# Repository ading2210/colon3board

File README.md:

# colon3board

This is a custom designed mechanical keyboard, created for the the [Hackpad](https://hackpad.hackclub.com/) event. It has a full sized 104 key layout, and a built in OLED display.

I designed this so I could get more practice with designing PCBs in KiCad and with modeling larger parts in Fusion 360. Also, I get to have a free keyboard in the end thanks to the grant from Hack Club. 

## BOM

### For PCB:
| Part                                  | Count (needed) | Count (purchased) | Price  | Shipping Cost | Link                                                                                          |
|---------------------------------------|----------------|-------------------|--------|---------------|-----------------------------------------------------------------------------------------------|
| Raspberry Pi Pico                     | 1              | 0                 | $0.00  | $0.00         | https://www.amazon.com/Raspberry-RP2040-microcontroller-Dual-core-Processor-1pc/dp/B0BK9CTMSV |
| SSD1306 128x32 OLED                   | 1              | 1                 | $2.32  | $0.00         | https://www.aliexpress.us/item/3256805123611667.html                                          |
| Cherry MX key switches                | 104            | 108               | $32.99 | $0.00         | https://www.amazon.com/Zjmehty-Switches-Mechanical-Pre-Lubed-Pin-Enhanced/dp/B0CF8DWDGF       |
| PBT Keycaps                           | 104            | 139               | $13.99 | $0.00         | https://www.amazon.com/Doubleshot-Mechanical-Keyboard-Compatiability-Keyboads/dp/B0F7H32LKC   |
| PCB Mount Stabilizers Kit             | 1              | 1                 | $9.99  | $0.00         | https://www.amazon.com/GLORIOUS-Stabilizer-Mechanical-Keyboards-Compatible/dp/B09MZKFLXP      |
| 1x4 2.54mm vertical female pin header | 1              | 1                 | $0.25  | $4.99         | https://www.digikey.com/en/products/detail/adam-tech/RS1-04-G/9829303                         |
| 1x4 2.54mm vertical male pin header   | 1              | 1                 | $0.20  | $0.00         | https://www.digikey.com/en/products/detail/metz-connect-usa-inc/PR20204VBNN/12342903          |
| MCP23008 IO expander                  | 1              | 1                 | $1.54  | $0.00         | https://www.digikey.com/en/products/detail/microchip-technology/MCP23008-E-P/735951           |
| 1N4148 diodes                         | 104            | 110               | $3.72  | $0.00         | https://www.digikey.com/en/products/detail/onsemi/1N4148-T50A/978509                          |
| PCB Fabrication from JLCPCB           | 1              | 5                 | $25.80 | $52.08        | https://jlcpcb.com/                                                                           |

### For Case:
- Case is 3d printed in PLA
- 6x M2x5 screw
- 4x M3x12 screw
- 4x M3x4 heat set inserts

## License

This project is licensed under the GNU GPL v3.

```
ading2210/colon3board - A custom mechanical keyboard
Copyright (C) 2025 ading2210

This program is free software: you can redistribute it and/or modify
it under the terms of the GNU General Public License as published by
the Free Software Foundation, either version 3 of the License, or
(at your option) any later version.

This program is distributed in the hope that it will be useful,
but WITHOUT ANY WARRANTY; without even the implied warranty of
MERCHANTABILITY or FITNESS FOR A PARTICULAR PURPOSE.  See the
GNU General Public License for more details.

You should have received a copy of the GNU General Public License
along with this program.  If not, see <https://www.gnu.org/licenses/>.
```

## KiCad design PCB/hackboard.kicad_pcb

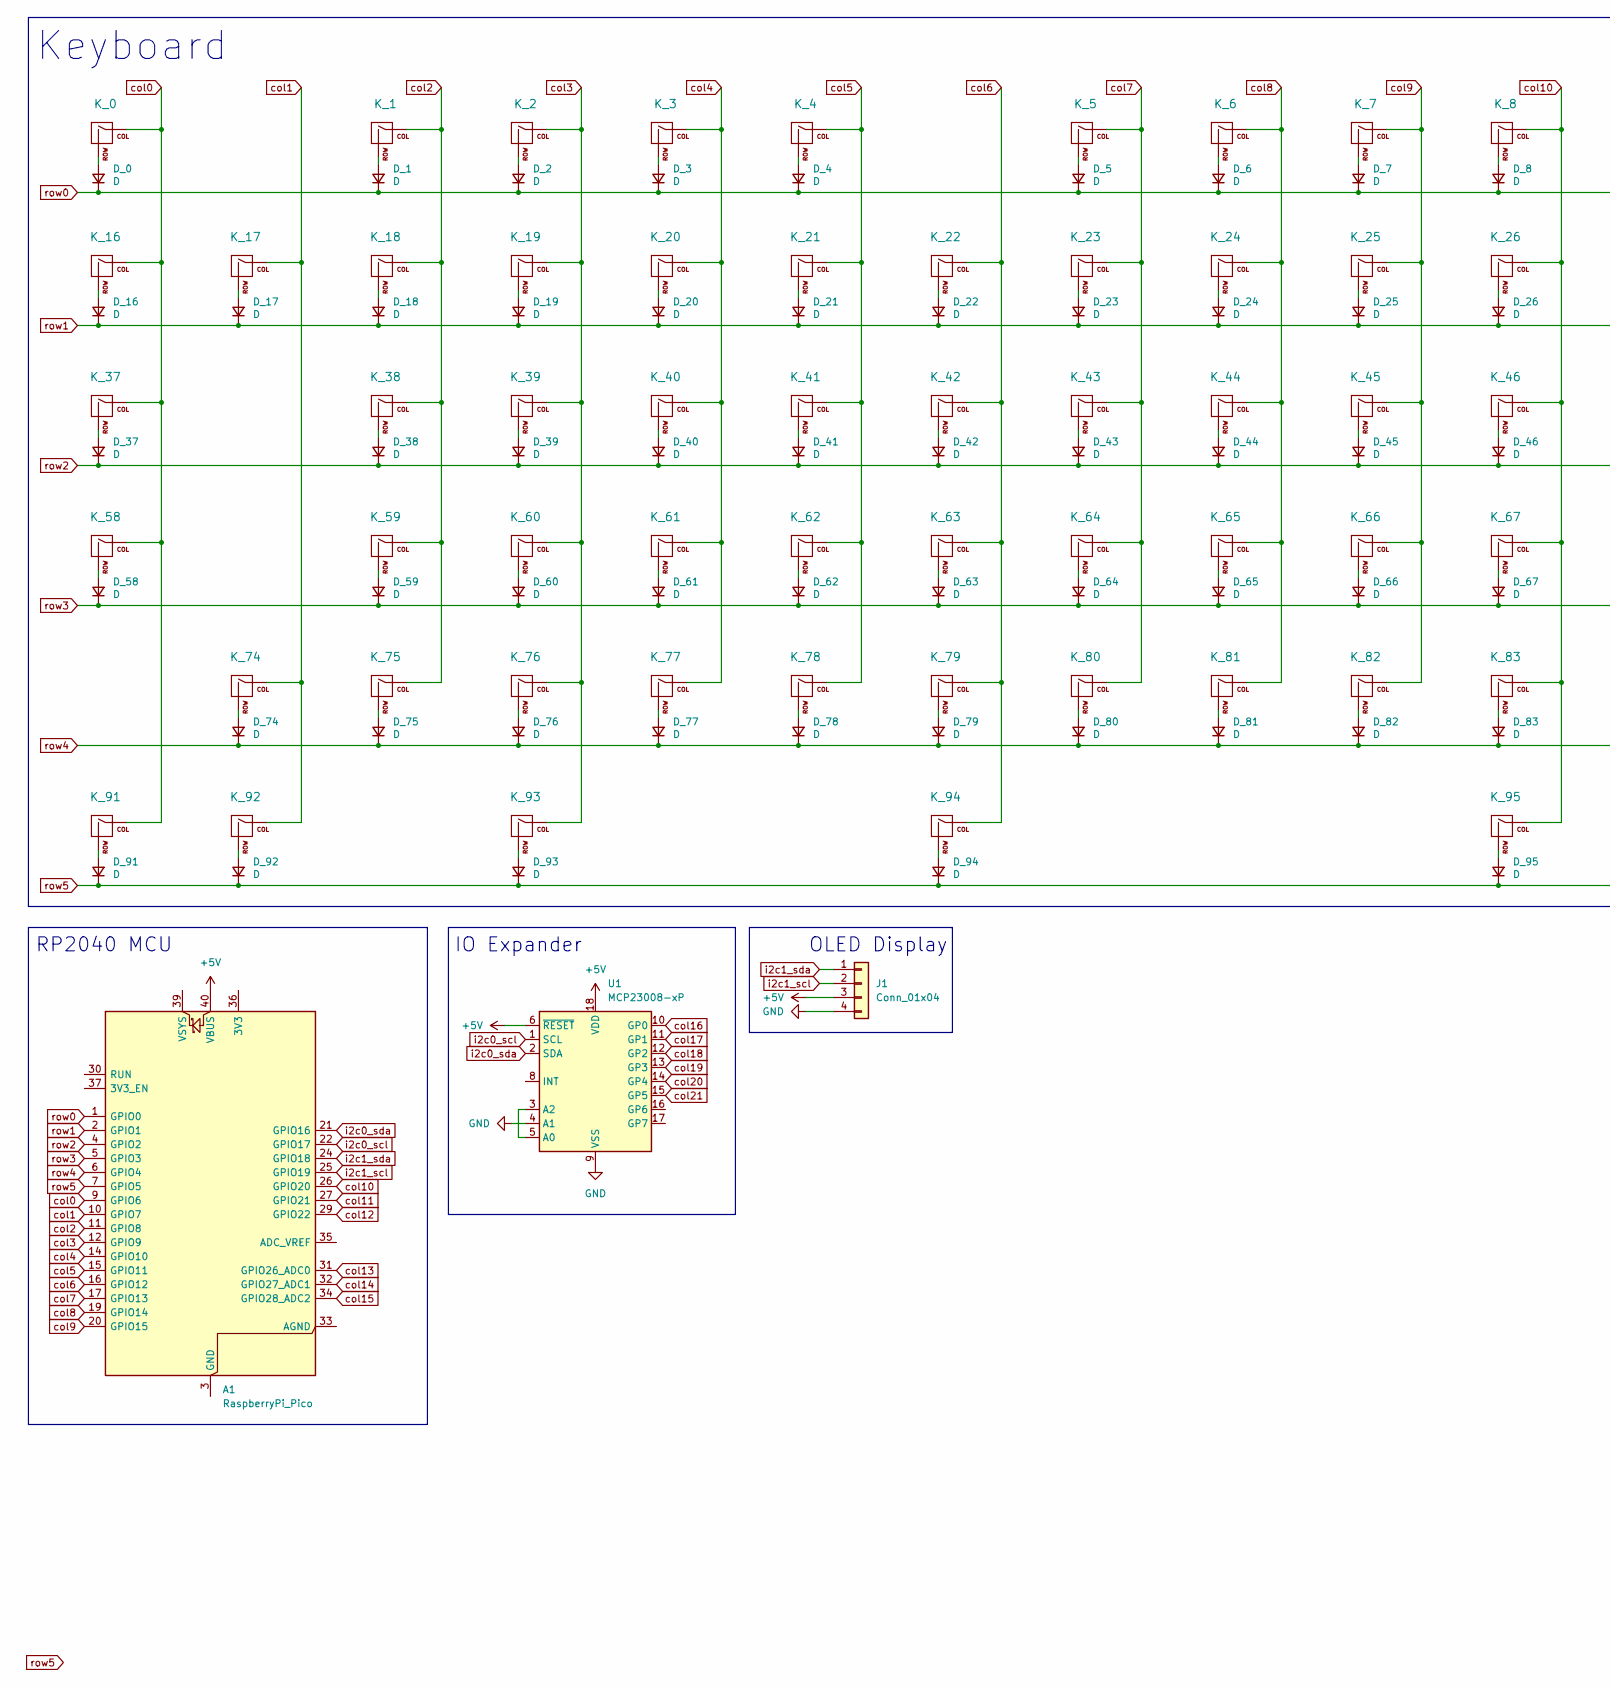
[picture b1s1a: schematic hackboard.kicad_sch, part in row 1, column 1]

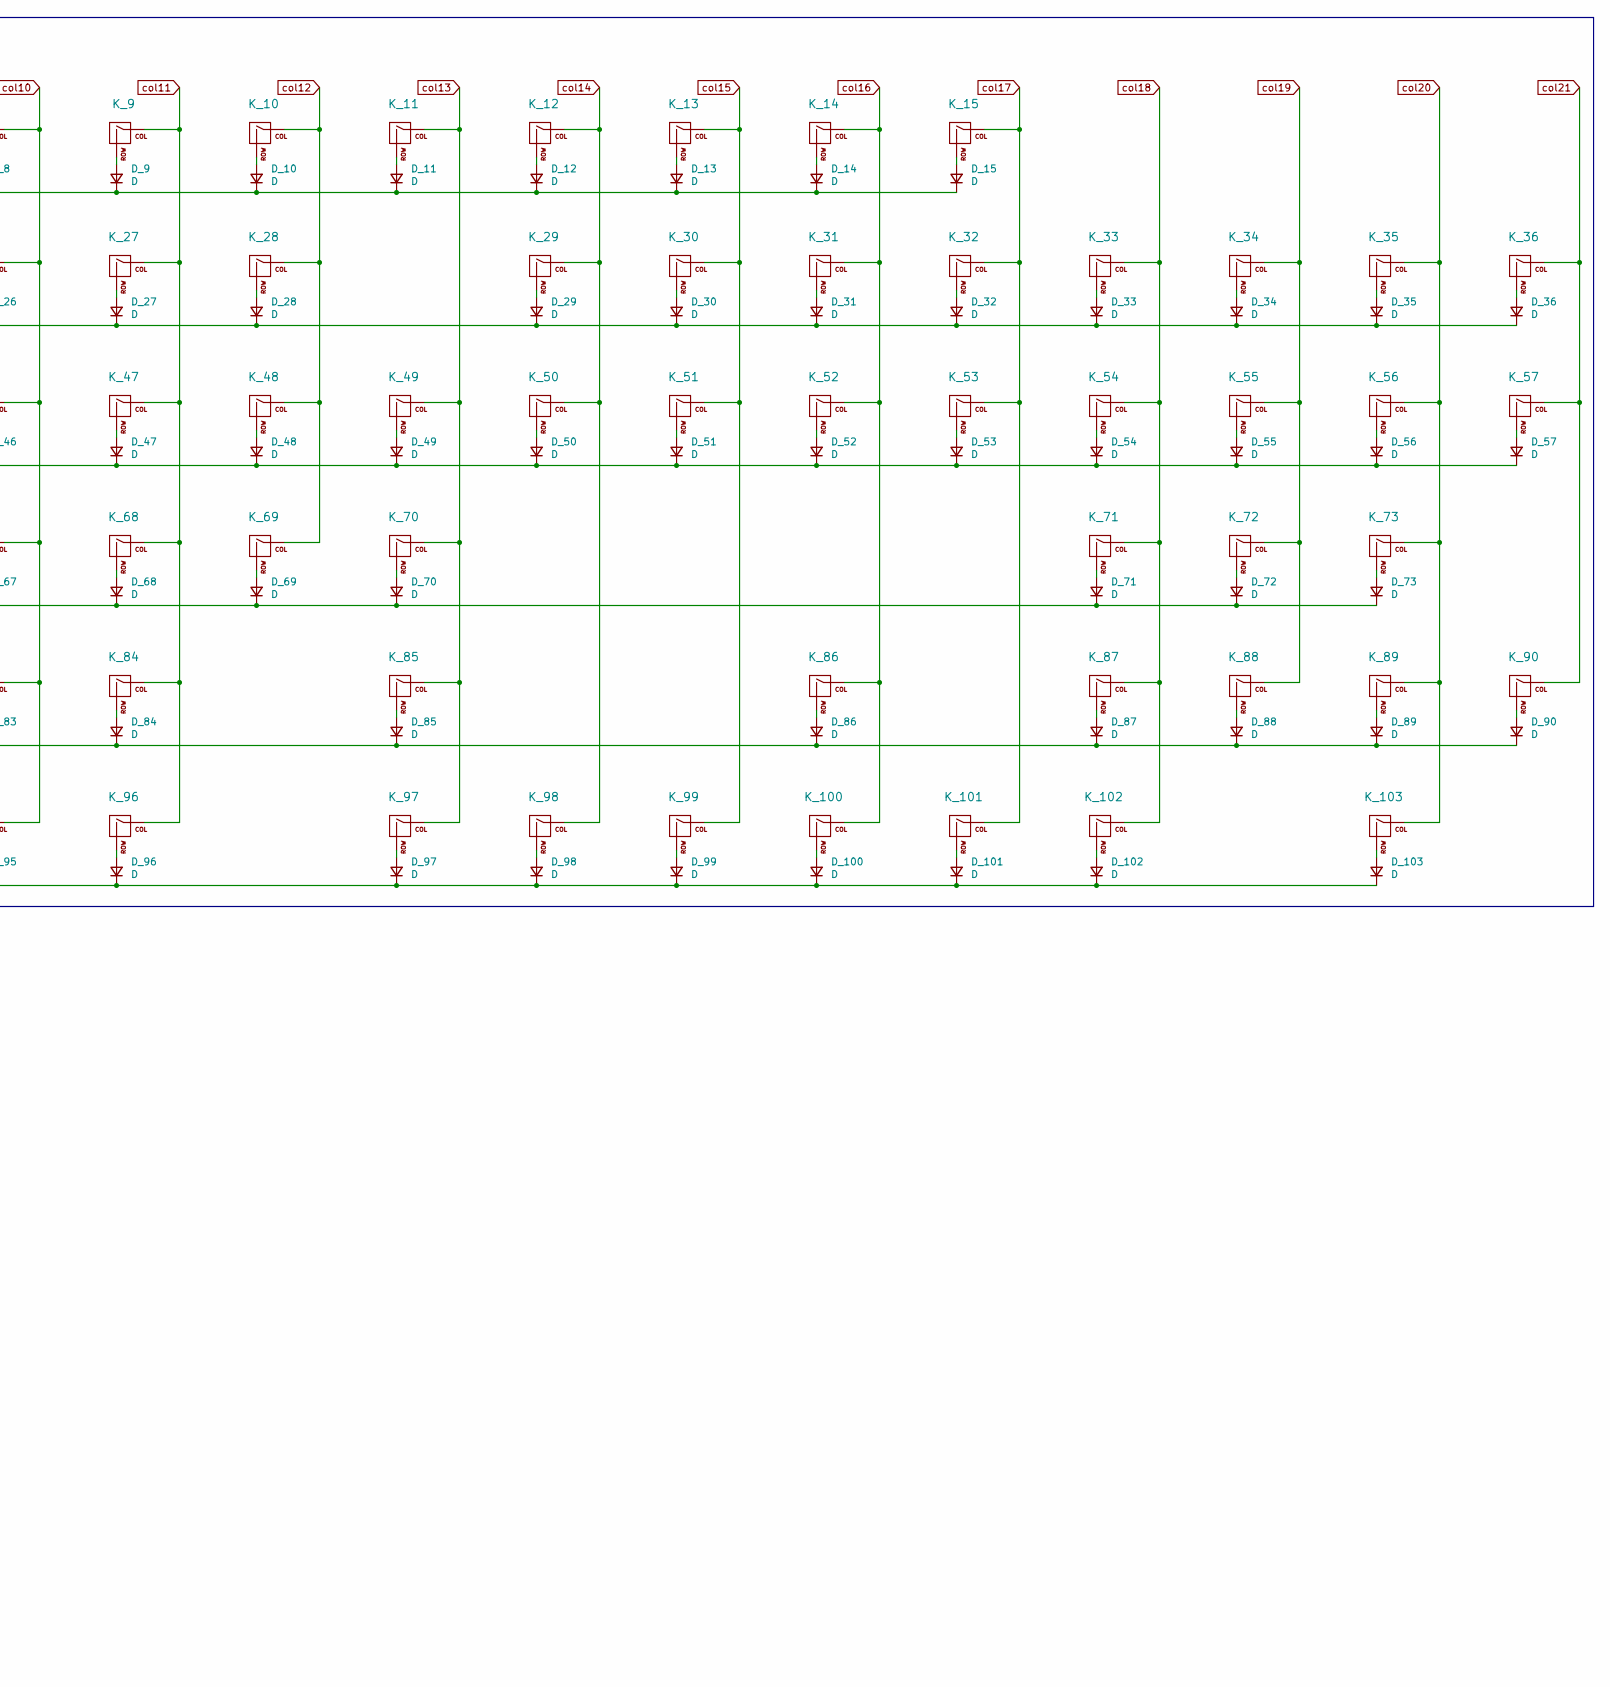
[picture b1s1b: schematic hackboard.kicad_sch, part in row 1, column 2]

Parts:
A1: RaspberryPi_Pico; RaspberryPi_Pico_Common_Unspecified
D_0, D_1, D_2, D_3, D_4, D_5, D_6, D_7, D_8, D_9, D_10, D_11, D_12, D_13, D_14, D_15, D_16, D_17, D_18, D_19, D_20, D_21, D_22, D_23, D_24, D_25, D_26, D_27, D_28, D_29, D_30, D_31, D_32, D_33, D_34, D_35, D_36, D_37, D_38, D_39, D_40, D_41, D_42, D_43, D_44, D_45, D_46, D_47, D_48, D_49, D_50, D_51, D_52, D_53, D_54, D_55, D_56, D_57, D_58, D_59, D_60, D_61, D_62, D_63, D_64, D_65, D_66, D_67, D_68, D_69, D_70, D_71, D_72, D_73, D_74, D_75, D_76, D_77, D_78, D_79, D_80, D_81, D_82, D_83, D_84, D_85, D_86, D_87, D_88, D_89, D_90, D_91, D_92, D_93, D_94, D_95, D_96, D_97, D_98, D_99, D_100, D_101, D_102, D_103: D; D_DO-35_SOD27_P7.62mm_Horizontal
J1: Conn_01x04; PinSocket_1x04_P2.54mm_Vertical_OLED
K_0, K_1, K_2, K_3, K_4, K_5, K_6, K_7, K_8, K_9, K_10, K_11, K_12, K_13, K_14, K_15, K_16, K_17, K_18, K_19, K_20, K_21, K_22, K_23, K_24, K_25, K_26, K_27, K_28, K_30, K_31, K_32, K_33, K_34, K_35, K_36, K_38, K_39, K_40, K_41, K_42, K_43, K_44, K_45, K_46, K_47, K_48, K_49, K_51, K_52, K_53, K_54, K_55, K_56, K_59, K_60, K_61, K_62, K_63, K_64, K_65, K_66, K_67, K_68, K_69, K_71, K_72, K_73, K_75, K_76, K_77, K_78, K_79, K_80, K_81, K_82, K_83, K_84, K_86, K_87, K_88, K_89, K_99, K_100, K_101, K_103: KEYSW; SW_Cherry_MX_1.00u_PCB
K_29, K_102: KEYSW; SW_Cherry_MX_2.00u_PCB
K_37, K_50: KEYSW; SW_Cherry_MX_1.50u_PCB
K_57, K_90: KEYSW; SW_Cherry_MX_2.00u_PCB_r1
K_58: KEYSW; SW_Cherry_MX_1.75u_PCB
K_70, K_74: KEYSW; SW_Cherry_MX_2.25u_PCB
K_85: KEYSW; SW_Cherry_MX_2.75u_PCB
K_91, K_92, K_93, K_95, K_96, K_97, K_98: KEYSW; SW_Cherry_MX_1.25u_PCB
K_94: KEYSW; SW_Cherry_MX_6.25u_PCB
U1: MCP23008-xP; DIP-18_W7.62mm

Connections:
+5V: A1.40 (VBUS), J1.3, U1.6 (~RESET), U1.18 (VDD)
GND: J1.4, U1.4 (A1), U1.9 (VSS)
unnamed: A1.3 (GND), A1.8 (GND), A1.13 (GND), A1.18 (GND), A1.23 (GND), A1.28 (GND), A1.38 (GND)
unnamed: D_0.2 (A), K_0.2 (ROW)
unnamed: D_1.2 (A), K_1.2 (ROW)
unnamed: D_2.2 (A), K_2.2 (ROW)
unnamed: D_3.2 (A), K_3.2 (ROW)
unnamed: D_4.2 (A), K_4.2 (ROW)
unnamed: D_5.2 (A), K_5.2 (ROW)
unnamed: D_6.2 (A), K_6.2 (ROW)
unnamed: D_7.2 (A), K_7.2 (ROW)
unnamed: D_8.2 (A), K_8.2 (ROW)
unnamed: D_9.2 (A), K_9.2 (ROW)
unnamed: D_10.2 (A), K_10.2 (ROW)
unnamed: D_11.2 (A), K_11.2 (ROW)
unnamed: D_12.2 (A), K_12.2 (ROW)
unnamed: D_13.2 (A), K_13.2 (ROW)
unnamed: D_14.2 (A), K_14.2 (ROW)
unnamed: D_15.2 (A), K_15.2 (ROW)
unnamed: D_16.2 (A), K_16.2 (ROW)
unnamed: D_17.2 (A), K_17.2 (ROW)
unnamed: D_18.2 (A), K_18.2 (ROW)
unnamed: D_19.2 (A), K_19.2 (ROW)
unnamed: D_20.2 (A), K_20.2 (ROW)
unnamed: D_21.2 (A), K_21.2 (ROW)
unnamed: D_22.2 (A), K_22.2 (ROW)
unnamed: D_23.2 (A), K_23.2 (ROW)
unnamed: D_24.2 (A), K_24.2 (ROW)
unnamed: D_25.2 (A), K_25.2 (ROW)
unnamed: D_26.2 (A), K_26.2 (ROW)
unnamed: D_27.2 (A), K_27.2 (ROW)
unnamed: D_28.2 (A), K_28.2 (ROW)
unnamed: D_29.2 (A), K_29.2 (ROW)
unnamed: D_30.2 (A), K_30.2 (ROW)
unnamed: D_31.2 (A), K_31.2 (ROW)
unnamed: D_32.2 (A), K_32.2 (ROW)
unnamed: D_33.2 (A), K_33.2 (ROW)
unnamed: D_34.2 (A), K_34.2 (ROW)
unnamed: D_35.2 (A), K_35.2 (ROW)
unnamed: D_36.2 (A), K_36.2 (ROW)
unnamed: D_37.2 (A), K_37.2 (ROW)
unnamed: D_38.2 (A), K_38.2 (ROW)
unnamed: D_39.2 (A), K_39.2 (ROW)
unnamed: D_40.2 (A), K_40.2 (ROW)
unnamed: D_41.2 (A), K_41.2 (ROW)
unnamed: D_42.2 (A), K_42.2 (ROW)
unnamed: D_43.2 (A), K_43.2 (ROW)
unnamed: D_44.2 (A), K_44.2 (ROW)
unnamed: D_45.2 (A), K_45.2 (ROW)
unnamed: D_46.2 (A), K_46.2 (ROW)
unnamed: D_47.2 (A), K_47.2 (ROW)
unnamed: D_48.2 (A), K_48.2 (ROW)
unnamed: D_49.2 (A), K_49.2 (ROW)
unnamed: D_50.2 (A), K_50.2 (ROW)
unnamed: D_51.2 (A), K_51.2 (ROW)
unnamed: D_52.2 (A), K_52.2 (ROW)
unnamed: D_53.2 (A), K_53.2 (ROW)
unnamed: D_54.2 (A), K_54.2 (ROW)
unnamed: D_55.2 (A), K_55.2 (ROW)
unnamed: D_56.2 (A), K_56.2 (ROW)
unnamed: D_57.2 (A), K_57.2 (ROW)
unnamed: D_58.2 (A), K_58.2 (ROW)
unnamed: D_59.2 (A), K_59.2 (ROW)
unnamed: D_60.2 (A), K_60.2 (ROW)
unnamed: D_61.2 (A), K_61.2 (ROW)
unnamed: D_62.2 (A), K_62.2 (ROW)
unnamed: D_63.2 (A), K_63.2 (ROW)
unnamed: D_64.2 (A), K_64.2 (ROW)
unnamed: D_65.2 (A), K_65.2 (ROW)
unnamed: D_66.2 (A), K_66.2 (ROW)
unnamed: D_67.2 (A), K_67.2 (ROW)
unnamed: D_68.2 (A), K_68.2 (ROW)
unnamed: D_69.2 (A), K_69.2 (ROW)
unnamed: D_70.2 (A), K_70.2 (ROW)
unnamed: D_71.2 (A), K_71.2 (ROW)
unnamed: D_72.2 (A), K_72.2 (ROW)
unnamed: D_73.2 (A), K_73.2 (ROW)
unnamed: D_74.2 (A), K_74.2 (ROW)
unnamed: D_75.2 (A), K_75.2 (ROW)
unnamed: D_76.2 (A), K_76.2 (ROW)
unnamed: D_77.2 (A), K_77.2 (ROW)
unnamed: D_78.2 (A), K_78.2 (ROW)
unnamed: D_79.2 (A), K_79.2 (ROW)
unnamed: D_80.2 (A), K_80.2 (ROW)
unnamed: D_81.2 (A), K_81.2 (ROW)
unnamed: D_82.2 (A), K_82.2 (ROW)
unnamed: D_83.2 (A), K_83.2 (ROW)
unnamed: D_84.2 (A), K_84.2 (ROW)
unnamed: D_85.2 (A), K_85.2 (ROW)
unnamed: D_86.2 (A), K_86.2 (ROW)
unnamed: D_87.2 (A), K_87.2 (ROW)
unnamed: D_88.2 (A), K_88.2 (ROW)
unnamed: D_89.2 (A), K_89.2 (ROW)
unnamed: D_90.2 (A), K_90.2 (ROW)
unnamed: D_91.2 (A), K_91.2 (ROW)
unnamed: D_92.2 (A), K_92.2 (ROW)
unnamed: D_93.2 (A), K_93.2 (ROW)
unnamed: D_94.2 (A), K_94.2 (ROW)
unnamed: D_95.2 (A), K_95.2 (ROW)
unnamed: D_96.2 (A), K_96.2 (ROW)
unnamed: D_97.2 (A), K_97.2 (ROW)
unnamed: D_98.2 (A), K_98.2 (ROW)
unnamed: D_99.2 (A), K_99.2 (ROW)
unnamed: D_100.2 (A), K_100.2 (ROW)
unnamed: D_101.2 (A), K_101.2 (ROW)
unnamed: D_102.2 (A), K_102.2 (ROW)
unnamed: D_103.2 (A), K_103.2 (ROW)
unnamed: U1.3 (A2), U1.5 (A0)
col0: A1.9 (GPIO6), K_0.1 (COL), K_16.1 (COL), K_37.1 (COL), K_58.1 (COL), K_91.1 (COL)
col1: A1.10 (GPIO7), K_17.1 (COL), K_74.1 (COL), K_92.1 (COL)
col2: A1.11 (GPIO8), K_1.1 (COL), K_18.1 (COL), K_38.1 (COL), K_59.1 (COL), K_75.1 (COL)
col3: A1.12 (GPIO9), K_2.1 (COL), K_19.1 (COL), K_39.1 (COL), K_60.1 (COL), K_76.1 (COL), K_93.1 (COL)
col4: A1.14 (GPIO10), K_3.1 (COL), K_20.1 (COL), K_40.1 (COL), K_61.1 (COL), K_77.1 (COL)
col5: A1.15 (GPIO11), K_4.1 (COL), K_21.1 (COL), K_41.1 (COL), K_62.1 (COL), K_78.1 (COL)
col6: A1.16 (GPIO12), K_22.1 (COL), K_42.1 (COL), K_63.1 (COL), K_79.1 (COL), K_94.1 (COL)
col7: A1.17 (GPIO13), K_5.1 (COL), K_23.1 (COL), K_43.1 (COL), K_64.1 (COL), K_80.1 (COL)
col8: A1.19 (GPIO14), K_6.1 (COL), K_24.1 (COL), K_44.1 (COL), K_65.1 (COL), K_81.1 (COL)
col9: A1.20 (GPIO15), K_7.1 (COL), K_25.1 (COL), K_45.1 (COL), K_66.1 (COL), K_82.1 (COL)
col10: A1.26 (GPIO20), K_8.1 (COL), K_26.1 (COL), K_46.1 (COL), K_67.1 (COL), K_83.1 (COL), K_95.1 (COL)
col11: A1.27 (GPIO21), K_9.1 (COL), K_27.1 (COL), K_47.1 (COL), K_68.1 (COL), K_84.1 (COL), K_96.1 (COL)
col12: A1.29 (GPIO22), K_10.1 (COL), K_28.1 (COL), K_48.1 (COL), K_69.1 (COL)
col13: A1.31 (GPIO26_ADC0), K_11.1 (COL), K_49.1 (COL), K_70.1 (COL), K_85.1 (COL), K_97.1 (COL)
col14: A1.32 (GPIO27_ADC1), K_12.1 (COL), K_29.1 (COL), K_50.1 (COL), K_98.1 (COL)
col15: A1.34 (GPIO28_ADC2), K_13.1 (COL), K_30.1 (COL), K_51.1 (COL), K_99.1 (COL)
col16: K_14.1 (COL), K_31.1 (COL), K_52.1 (COL), K_86.1 (COL), K_100.1 (COL), U1.10 (GP0)
col17: K_15.1 (COL), K_32.1 (COL), K_53.1 (COL), K_101.1 (COL), U1.11 (GP1)
col18: K_33.1 (COL), K_54.1 (COL), K_71.1 (COL), K_87.1 (COL), K_102.1 (COL), U1.12 (GP2)
col19: K_34.1 (COL), K_55.1 (COL), K_72.1 (COL), K_88.1 (COL), U1.13 (GP3)
col20: K_35.1 (COL), K_56.1 (COL), K_73.1 (COL), K_89.1 (COL), K_103.1 (COL), U1.14 (GP4)
col21: K_36.1 (COL), K_57.1 (COL), K_90.1 (COL), U1.15 (GP5)
i2c0_scl: A1.22 (GPIO17), U1.1 (SCL)
i2c0_sda: A1.21 (GPIO16), U1.2 (SDA)
i2c1_scl: A1.25 (GPIO19), J1.2
i2c1_sda: A1.24 (GPIO18), J1.1
row0: A1.1 (GPIO0), D_0.1 (K), D_1.1 (K), D_2.1 (K), D_3.1 (K), D_4.1 (K), D_5.1 (K), D_6.1 (K), D_7.1 (K), D_8.1 (K), D_9.1 (K), D_10.1 (K), D_11.1 (K), D_12.1 (K), D_13.1 (K), D_14.1 (K), D_15.1 (K)
row1: A1.2 (GPIO1), D_16.1 (K), D_17.1 (K), D_18.1 (K), D_19.1 (K), D_20.1 (K), D_21.1 (K), D_22.1 (K), D_23.1 (K), D_24.1 (K), D_25.1 (K), D_26.1 (K), D_27.1 (K), D_28.1 (K), D_29.1 (K), D_30.1 (K), D_31.1 (K), D_32.1 (K), D_33.1 (K), D_34.1 (K), D_35.1 (K), D_36.1 (K)
row2: A1.4 (GPIO2), D_37.1 (K), D_38.1 (K), D_39.1 (K), D_40.1 (K), D_41.1 (K), D_42.1 (K), D_43.1 (K), D_44.1 (K), D_45.1 (K), D_46.1 (K), D_47.1 (K), D_48.1 (K), D_49.1 (K), D_50.1 (K), D_51.1 (K), D_52.1 (K), D_53.1 (K), D_54.1 (K), D_55.1 (K), D_56.1 (K), D_57.1 (K)
row3: A1.5 (GPIO3), D_58.1 (K), D_59.1 (K), D_60.1 (K), D_61.1 (K), D_62.1 (K), D_63.1 (K), D_64.1 (K), D_65.1 (K), D_66.1 (K), D_67.1 (K), D_68.1 (K), D_69.1 (K), D_70.1 (K), D_71.1 (K), D_72.1 (K), D_73.1 (K)
row4: A1.6 (GPIO4), D_74.1 (K), D_75.1 (K), D_76.1 (K), D_77.1 (K), D_78.1 (K), D_79.1 (K), D_80.1 (K), D_81.1 (K), D_82.1 (K), D_83.1 (K), D_84.1 (K), D_85.1 (K), D_86.1 (K), D_87.1 (K), D_88.1 (K), D_89.1 (K), D_90.1 (K)
row5: A1.7 (GPIO5), D_91.1 (K), D_92.1 (K), D_93.1 (K), D_94.1 (K), D_95.1 (K), D_96.1 (K), D_97.1 (K), D_98.1 (K), D_99.1 (K), D_100.1 (K), D_101.1 (K), D_102.1 (K), D_103.1 (K)

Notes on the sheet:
Keyboard
IO Expander
RP2040 MCU
OLED Display

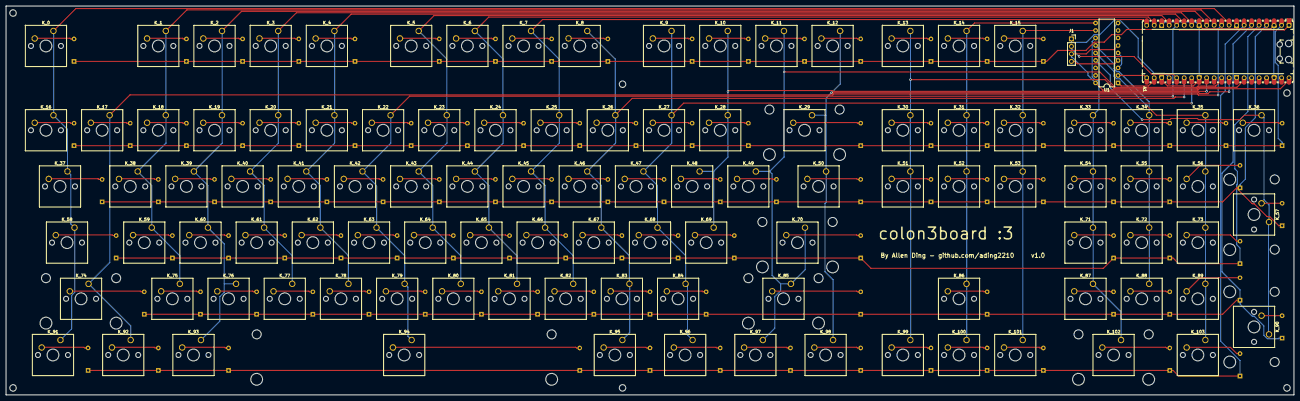
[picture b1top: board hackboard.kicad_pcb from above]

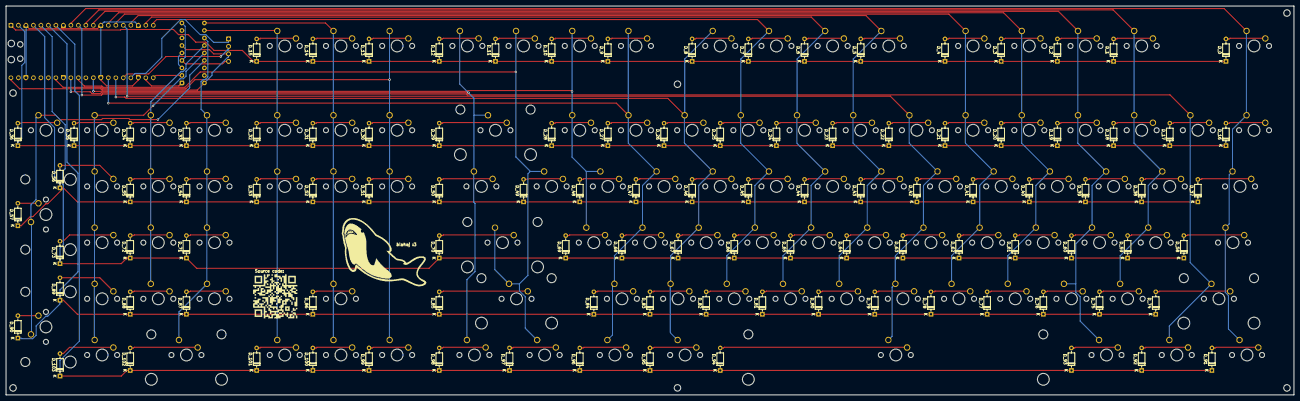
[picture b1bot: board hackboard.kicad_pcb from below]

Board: 2 copper layers, 436.6 x 131.8 mm, 219 parts (106 on the bottom side), 140 nets.

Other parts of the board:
G1, G2: LOGO
H1, H2, H3, H4, H5, H6: MountingHole_2.2mm_M2

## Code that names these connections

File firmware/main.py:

import board
import busio
import digitalio

from kmk.kmk_keyboard import KMKKeyboard
from kmk.scanners.keypad import MatrixScanner
from kmk.extensions.international import International
from kmk.keys import KC

from adafruit_mcp230xx.mcp23008 import MCP23008

#set up io expander
i2c = busio.I2C(board.SCL1, board.SDA1)
mcp = MCP23008(i2c)
mcp_pins = [mcp.get_pin(i) for i in range(6)]

#set up keyboard
keyboard = KMKKeyboard()
macros = Macros()
keyboard.modules.append(macros)
keyboard.extensions.append(International())

#define row/col pins
COL_PINS = [
  board.GP6, board.GP7, board.GP8, board.GP9, board.GP10, #col0 - col4
  board.GP11, board.GP12, board.GP13, board.GP14, board.GP15, #col5 - col9
  board.GP20, board.GP21, board.GP22, board.GP26, board.GP27, #col10 - col14
  board.GP28, mcp_pins[0], mcp_pins[1], mcp_pins[2], mcp_pins[3], #col15 - col19
  mcp_pins[4], mcp_pins[5] #col20-col21
]
ROW_PINS = [
  board.GP0, board.GP1, board.GP2, board.GP3, board.GP4, #row0-row4
  board.GP5 #row5
]

#setup key matrix
keyboard.matrix = MatrixScanner(
  column_pins = COL_PINS,
  row_pins = ROW_PINS
)

#alias for cleaner key map
_____ = KC.NO

#setup key map
keyboard.keymap = [
  [KC.ESC,  _____,   KC.F1, KC.F2,   KC.F3, KC.F4, _____,  KC.F5, KC.F6, KC.F7,   KC.F8,   KC.F9,   KC.F10,  KC.11,   KC.F12,   KC.PSCR, KC.SLCK, KC.PAUS, _____,   _____,   _____,   _____  ],
  [KC.GRV,  KC.N1,   KC.N2, KC.N3,   KC.N4, KC.N5, KC.N6,  KC.N7, KC.N8, KC.N9,   KC.N0,   KC.MINS, KC.EQL,  _____,   KC.BSPC,  KC.INS,  KC.HOME, KC.PGUP, KC.NLCK, KC.PSLS, KC.PAST, KC.PMNS],
  [KC.TAB,  _____,   KC.Q,  KC.W,    KC.E,  KC.R,  KC.T,   KC.Y,  KC.U,  KC.I,    KC.O,    KC.P,    KC.LBRC, KC.RBRC, KC.BSLC,  KC.DEL,  KC.END,  KC.PGDN, KC.P7,   KC.P8,   KC.P9,   KC.PPLS],
  [KC.CAPS, _____,   KC.A,  KC.S,    KC.D,  KC.F,  KC.G,   KC.H,  KC.J,  KC.K,    KC.L,    KC.SCLN, KC.QUOT, KC.ENT,  _____,    _____,   _____,   _____,   KC.P4,   KC.P5,   KC.P6,   _____  ],
  [_____,   KC.LSFT, KC.Z,  KC.X,    KC.C,  KC.V,  KC.B,   KC.N,  KC.M,  KC.COMM, KC.DOT,  KC.SLSH, _____,   KC.RSFT, _____,    _____,   KC.UP,   _____,   KC.P1,   KC.P2,   KC.P3,   KC.PENT],
  [KC.LCTL, KC.LWIN, _____, KC.LALT, _____, _____, KC.SPC, _____, _____, _____,   KC.RALT, KC.RWIN, _____,   KC.MENU, KC.RCTL,  KC.LEFT, KC.DOWN, KC.RGHT, KC.P0,   _____,   KC.PDOT, _____  ]
]

if __name__ == "__main__":
  keyboard.go()

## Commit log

2025-03-24 add initial kicad files
2025-03-25 add submodules for pi pico, files for oled
2025-03-25 add pcb routing and 3d model
2025-03-25 add 3d models for all key switches and components
2025-03-27 silkscreen art and mounting holes
2025-03-28 initial version of case cad model
2025-03-31 fix missing row5 connection on pcb
2025-03-31 add keyboard firmware
2025-03-31 add license and bom
2025-03-31 add readme
2025-03-31 add images to readme
2025-10-13 update bom and add production files
2025-10-16 update bom
